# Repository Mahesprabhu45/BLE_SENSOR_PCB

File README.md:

# 🛠 Precision PCB Project

This repository features a PCB that I **designed using KiCad and fully assembled**, including component placement, soldering, routing validation, and hardware testing.  
The project demonstrates an end-to-end real-world PCB development and assembly workflow.

---

### 🔧 What I Did

- Designed the **schematic and PCB layout in KiCad**
- Routed tracks and finalized footprints
- Exported and verified **Gerber files**
- Assembled and soldered all components
- Performed **continuity and functional testing** using a digital multimeter
- Debugged minor soldering errors and improved stability

---

### 🧠 Skills Gained

- PCB design workflow using **KiCad**
- Trace routing, net management & DRC handling
- Soldering and real hardware assembly practice
- Debugging using multimeter and visual inspection
- Understanding PCB tolerances and real-world constraints

---

### 💻 System Requirements (To Open or Modify This Project)

| Component | Minimum | Recommended |
|----------|---------|-------------|
| OS | Windows 10 / Linux / macOS | Windows 11 / Ubuntu |
| RAM | 4GB | 8GB or more |
| Storage | 2GB free | 5GB free |
| CPU | Dual-Core | Quad-Core or higher |
| GPU | Integrated graphics works | Dedicated GPU improves rendering (optional) |
| Software | KiCad **7.0+** | Latest KiCad stable release |

> ⚠️ Note: A graphics card is **not required**, but helps with faster 3D rendering and smoother UI in large designs.

---

### 🧰 Tools Used

- **Software:** KiCad, Gerber Viewer, 3D PCB Viewer  
- **Hardware Tools:** Soldering iron, flux, tweezers, DMM, cutter  
- **Components:** Resistors, capacitors, IC socket, pin headers, connectors  

---

### 🧭 Alternative Websites / Tools for PCB Designing

| Platform | Type | Best For |
|----------|------|----------|
| **EasyEDA** | Browser-Based | Beginners & quick designs (JLCPCB integration) |
| **Altium Designer** | Professional | Industry-level PCB design |
| **Fusion 360 Electronics** | Cloud + CAD | Projects with enclosures or mechanical integration |
| **Proteus** | Simulation + PCB | When circuit simulation + PCB design is needed |
| **EAGLE (Legacy)** | Autodesk | Still usable, now merged into Fusion 360 |

---

⭐ If you find this project useful or interesting, feel free to **star the repository!**

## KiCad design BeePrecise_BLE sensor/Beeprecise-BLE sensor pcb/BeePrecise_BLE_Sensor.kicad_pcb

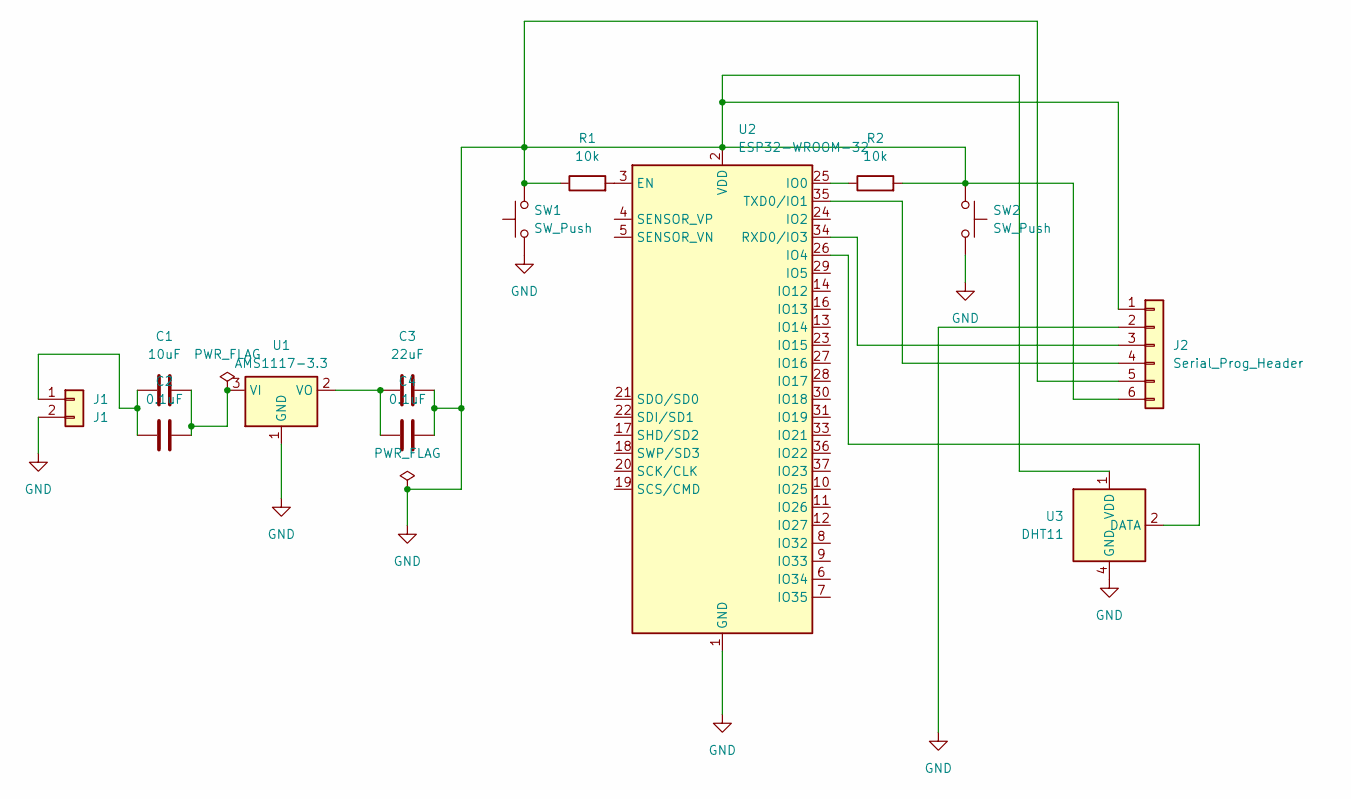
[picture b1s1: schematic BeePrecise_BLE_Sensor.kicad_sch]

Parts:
C1: 10uF; C_0805_2012Metric
C2, C4: 0.1uF; C_0805_2012Metric
C3: 22uF; C_0805_2012Metric
J1: J1; PinHeader_1x02_P2.54mm_Vertical
J2: Serial_Prog_Header; PinHeader_1x06_P2.54mm_Vertical
R1, R2: 10k; R_0805_2012Metric
SW1, SW2: SW_Push; SW_SPST_B3U-1000P
U1: AMS1117-3.3; SOT-223-3_TabPin2
U2: ESP32-WROOM-32
U3: DHT11; PinHeader_1x04_P2.54mm_Vertical

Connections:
GND: C3.2, C4.2, J1.2, J2.1, J2.2, J2.5, J2.6, R1.1, R2.2, SW1.1, SW1.2, SW2.1, SW2.2, U1.1 (GND), U2.1 (GND), U2.2 (VDD), U2.15 (GND), U2.38 (GND), U2.39 (GND), U3.1 (VDD), U3.4 (GND)
unnamed: C1.1, C2.1, J1.1
unnamed: J2.3, U2.34 (RXD0/IO3)
unnamed: J2.4, U2.35 (TXD0/IO1)
unnamed: C1.2, C2.2, U1.3 (VI)
unnamed: C3.1, C4.1, U1.2 (VO)
unnamed: R1.2, U2.3 (EN)
unnamed: R2.1, U2.25 (IO0)
unnamed: U2.26 (IO4), U3.2 (DATA)

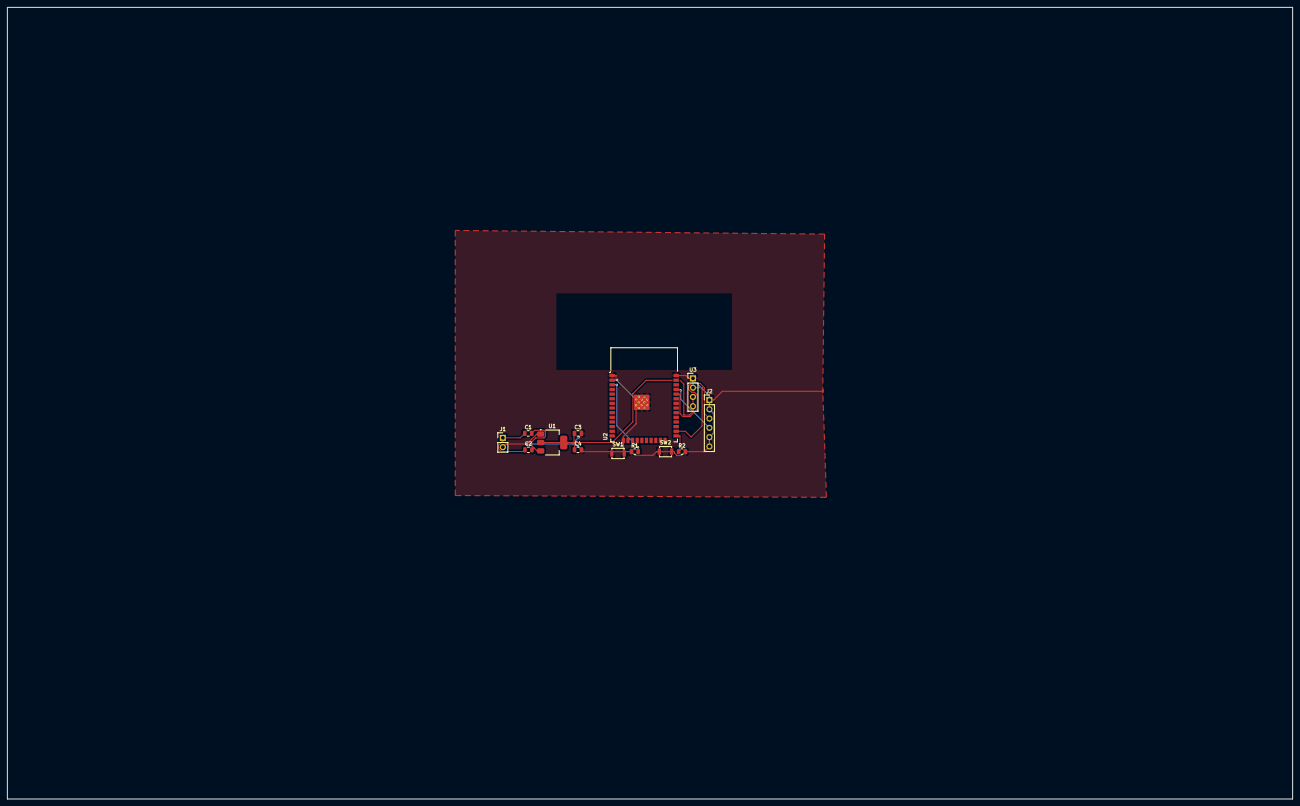
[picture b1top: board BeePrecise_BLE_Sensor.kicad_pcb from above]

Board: 2 copper layers, 351.5 x 216.5 mm, 13 parts (0 on the bottom side), 9 nets.

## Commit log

2025-11-26 Files added
